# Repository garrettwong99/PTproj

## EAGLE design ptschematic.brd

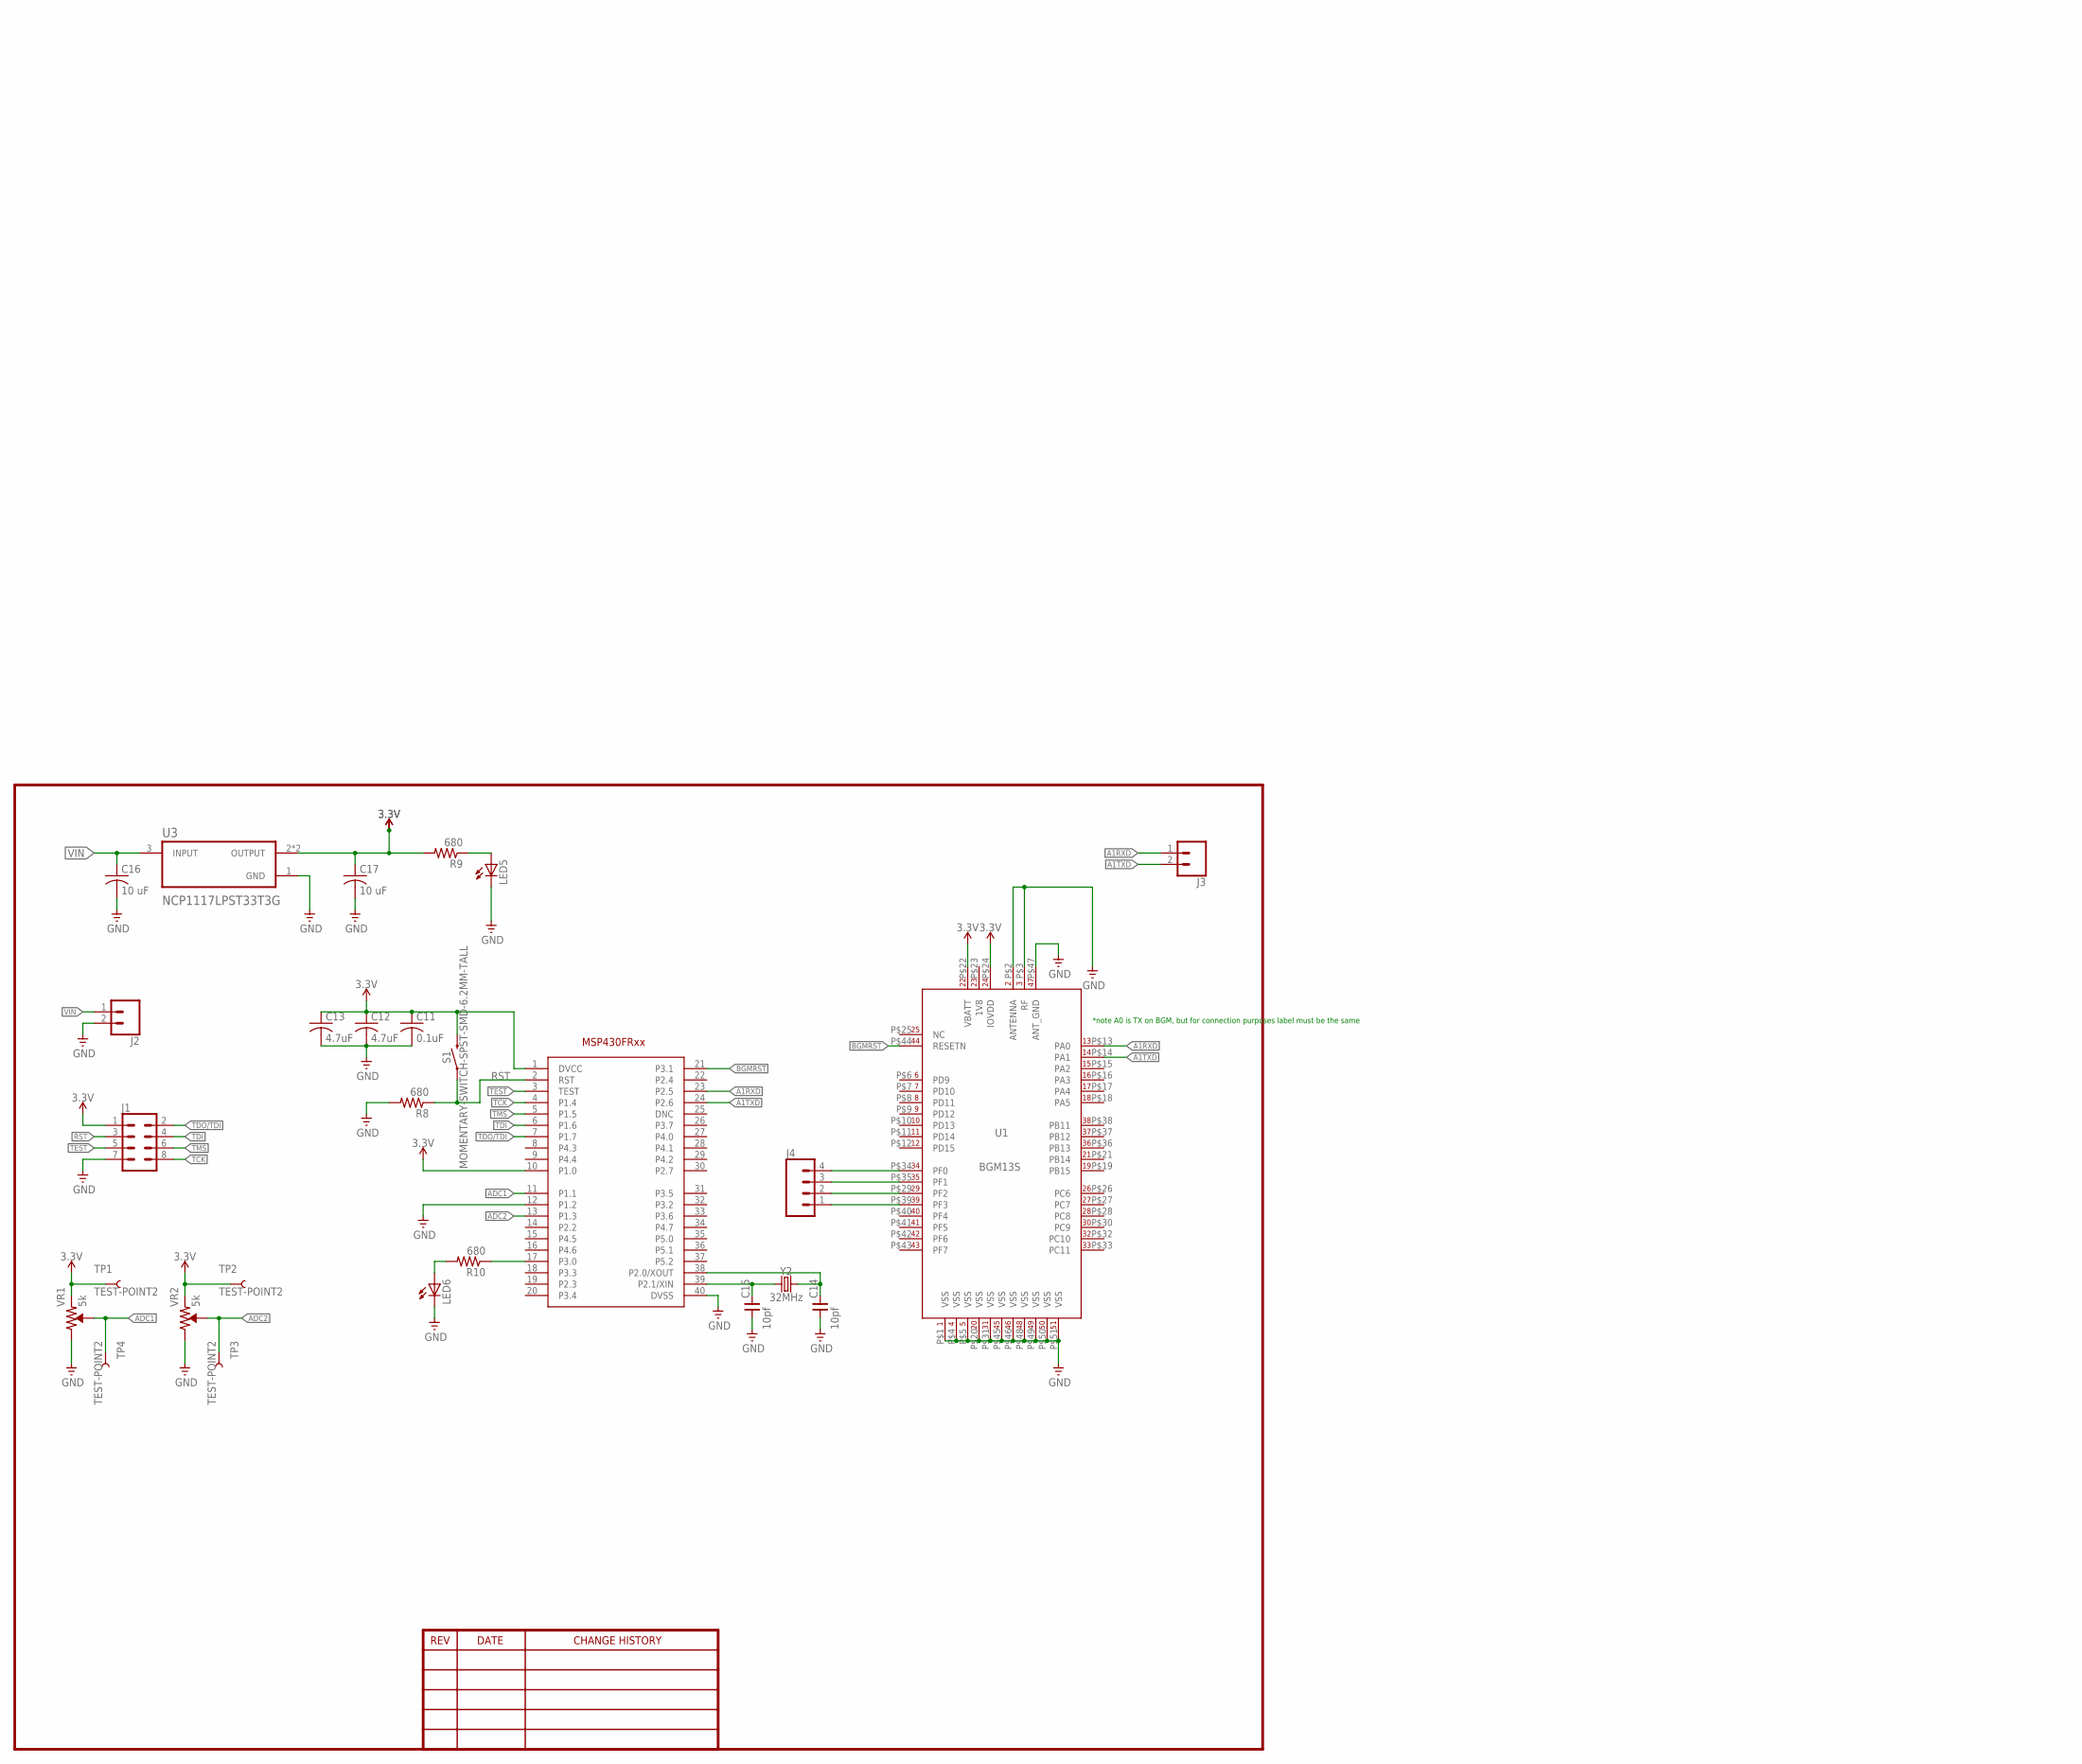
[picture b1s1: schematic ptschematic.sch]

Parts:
C11: 0.1uF; C0805
C12, C13: 4.7uF; C0805
C14, C15: 10pf; 0805
C16, C17: 10 uF; C0805
J1: CONN_04X2; 2X4
J2, J3: CONN_02; 1X02
J4: CONN_04; 1X04
LED5, LED6: LEDCHIPLED_0805; CHIPLED_0805
R8, R9, R10: 680; R0805
S1: MOMENTARY-SWITCH-SPST-SMD-6.2MM-TALL; TACTILE_SWITCH_SMD_6.2MM_TALL
TP1, TP2, TP3, TP4: TEST-POINT2; PAD.02X.02
U1: BGM13S
U3: NCP1117LPST33T3G; SOT230P700X175-4N
U$1: MSP340FR247; QFN-40
VR1, VR2: 5k; TRIMPOT-SMD-5MM
Y2: 32MHz; CRYSTAL-SMD-2.0X1.6MM

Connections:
1V8: U1.P$23 (1V8)
3.3V: C11.1, C12.1, C13.1, C17.1, J1.1, R9.2, S1.B2 (2), TP1.P$1, TP2.P$1, U1.P$22 (VBATT), U1.P$24 (IOVDD), U3.2 (OUTPUT), U3.4 (OUTPUT), U$1.1 (DVCC), U$1.10 (P1.0), VR1.A (CCW), VR2.A (CCW)
A1RXD: J3.1, U1.P$13 (PA0), U$1.23 (P2.5)
A1TXD: J3.2, U1.P$14 (PA1), U$1.24 (P2.6)
ADC1: TP4.P$1, U$1.11 (P1.1), VR1.B (WIPER)
ADC2: TP3.P$1, U$1.13 (P1.3), VR2.B (WIPER)
BGMRST: U1.P$44 (RESETN), U$1.21 (P3.1)
GND: C11.2, C12.2, C13.2, C14.1, C15.1, C16.2, C17.2, J1.7, J2.2, LED5.C, LED6.C, R8.2, U1.P$1 (VSS), U1.P$2 (ANTENNA), U1.P$3 (RF), U1.P$4 (VSS), U1.P$5 (VSS), U1.P$20 (VSS), U1.P$31 (VSS), U1.P$45 (VSS), U1.P$46 (VSS), U1.P$47 (ANT_GND), U1.P$48 (VSS), U1.P$49 (VSS), U1.P$50 (VSS), U1.P$51 (VSS), U3.1 (GND), U$1.12 (P1.2), U$1.40 (DVSS), VR1.C (CW), VR2.C (CW)
unnamed: J4.4, U1.P$34 (PF0)
unnamed: J4.3, U1.P$35 (PF1)
unnamed: J4.2, U1.P$29 (PF2)
unnamed: J4.1, U1.P$39 (PF3)
unnamed: LED5.A, R9.1
unnamed: C14.2, U$1.38 (P2.0/XOUT), Y2.3 (2)
unnamed: C15.2, U$1.39 (P2.1/XIN), Y2.1
unnamed: R10.1, U$1.17 (P3.0)
unnamed: LED6.A, R10.2
RST: J1.3, R8.1, S1.A2 (1), U$1.2 (RST)
TCK: J1.8, U$1.4 (P1.4)
TDI: J1.4, U$1.6 (P1.6)
TDO/TDI: J1.2, U$1.7 (P1.7)
TEST: J1.5, U$1.3 (TEST)
TMS: J1.6, U$1.5 (P1.5)
VIN: C16.1, J2.1, U3.3 (INPUT)

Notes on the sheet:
*note A0 is TX on BGM, but for connection purposes label must be the same

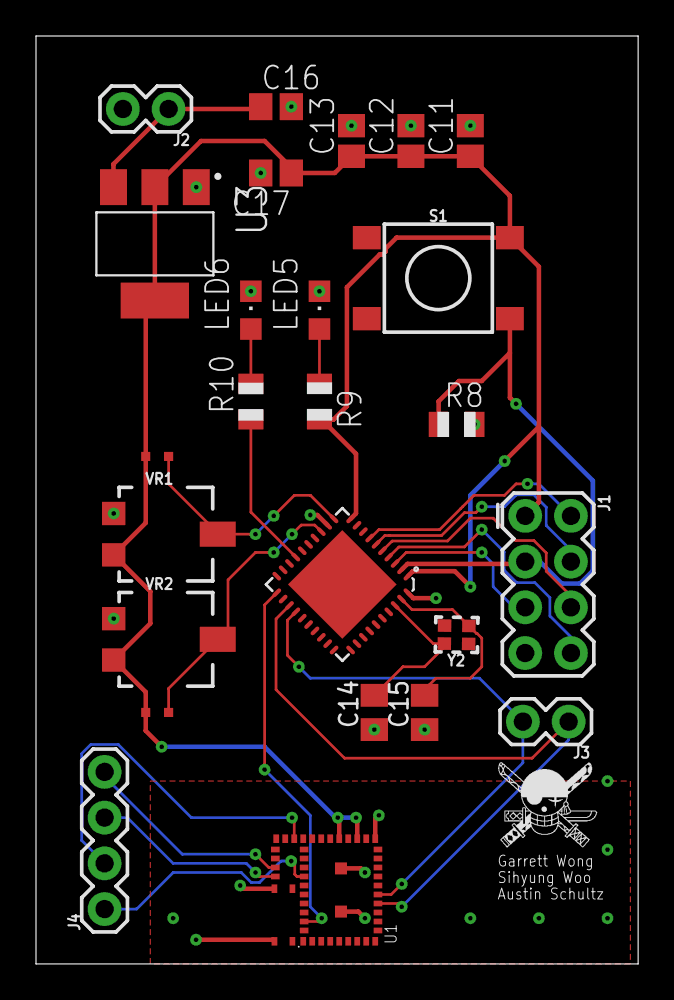
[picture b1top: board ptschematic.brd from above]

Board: 2 copper layers, 33.5 x 51.6 mm, 27 parts (0 on the bottom side), 23 nets.

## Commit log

2019-05-28 made library for coprocessor, and started eagle sch
2019-05-29 updated library and started schematic
2019-06-04 made changes to lbr and sch
2019-06-04 changes to sch and brd
2019-06-05 Organized board
2019-06-05 Started board routing
2019-06-05 finished tracing BGM
2019-06-06 updated board and schematic
2019-06-06 final updated with BOM
2019-06-06 put names and logo
2019-06-07 Final Board and Gerber files

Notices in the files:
parts and their libraries:
SparkFun-Connectors: Licensing: Creative Commons ShareAlike 4.0 International - https://creativecommons.org/licenses/by-sa/4.0
dframes: Copyright (C) 2004, Bob Starr (bobstarr@mindspring.com)
